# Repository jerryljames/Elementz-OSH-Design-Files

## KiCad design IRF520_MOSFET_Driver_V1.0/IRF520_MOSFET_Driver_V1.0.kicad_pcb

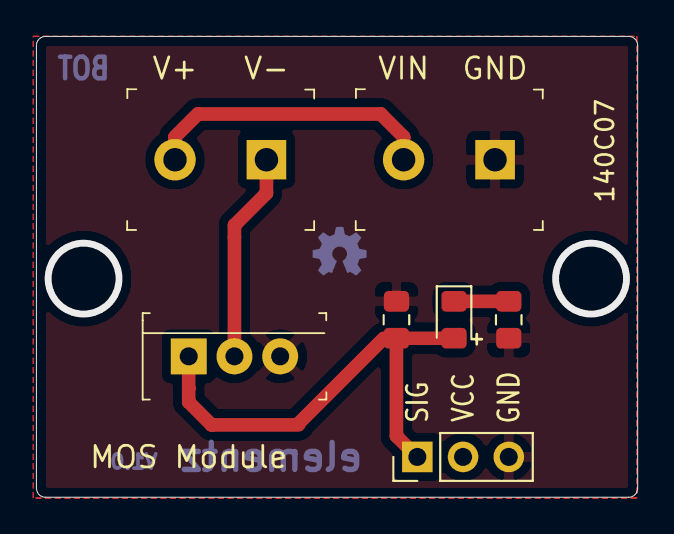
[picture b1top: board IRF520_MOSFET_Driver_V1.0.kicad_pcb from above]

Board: 2 copper layers, 33.4 x 25.6 mm, 7 parts (0 on the bottom side), 5 nets.

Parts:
D1: RED; LED_0805_2012Metric_Pad1.15x1.40mm_HandSolder
J1: Conn_01x03_Male; PinHeader_1x03_P2.54mm_Vertical
J2, J3: 1935161; Term_Block_1x2_P5.08MM
Q1: IRF520PBF; TO-220-3
R1, R2: 1K; R_0805_2012Metric_Pad1.15x1.40mm_HandSolder

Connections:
/SIG: D1.2, J1.1, Q1.1, R1.1
/V+: J2.2, J3.2
/V-: J2.1, Q1.2
GND: J1.3, J3.1, Q1.3, R1.2, R2.2
unnamed: D1.1, R2.1

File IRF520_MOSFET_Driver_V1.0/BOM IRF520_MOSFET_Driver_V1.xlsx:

Reference | Quantity | Value | Footprint | Category | Description | Digi-Key_PN | Family | MPN | Manufacturer | Status | DK_Datasheet_Link | DK_Detail_Page
D1 | 1 | RED | LED_SMD:LED_0805_2012Metric_Pad1.15x1.40mm_HandSolder
J1 | 1 | Conn_01x03_Male | Connector_PinHeader_2.54mm:PinHeader_1x03_P2.54mm_Horizontal
J2 J3 | 2 | 1935161 | TerminalBlock:TerminalBlock_Altech_AK300-2_P5.00mm | Connectors, Interconnects | TERM BLK 2POS SIDE ENTRY 5MM PCB | 277-1667-ND | Terminal Blocks - Wire to Board | 1935161 | Phoenix Contact | Active | https://media.digikey.com/pdf/Data%20Sheets/Phoenix%20Contac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 | /product-detail/en/phoenix-contact/1935161/277-1667-ND/568614
Q1 | 1 | IRF520PBF | digikey-footprints:TO-220-3 | Discrete Semiconductor Products | MOSFET N-CH 100V 9.2A TO-220-3 | IRF520PBF-ND | Transistors - FETs, MOSFETs - Single | IRF520PBF | Vishay Siliconix | Active
R1 R2 | 2 | 1K | Resistor_SMD:R_0805_2012Metric_Pad1.15x1.40mm_HandSolder

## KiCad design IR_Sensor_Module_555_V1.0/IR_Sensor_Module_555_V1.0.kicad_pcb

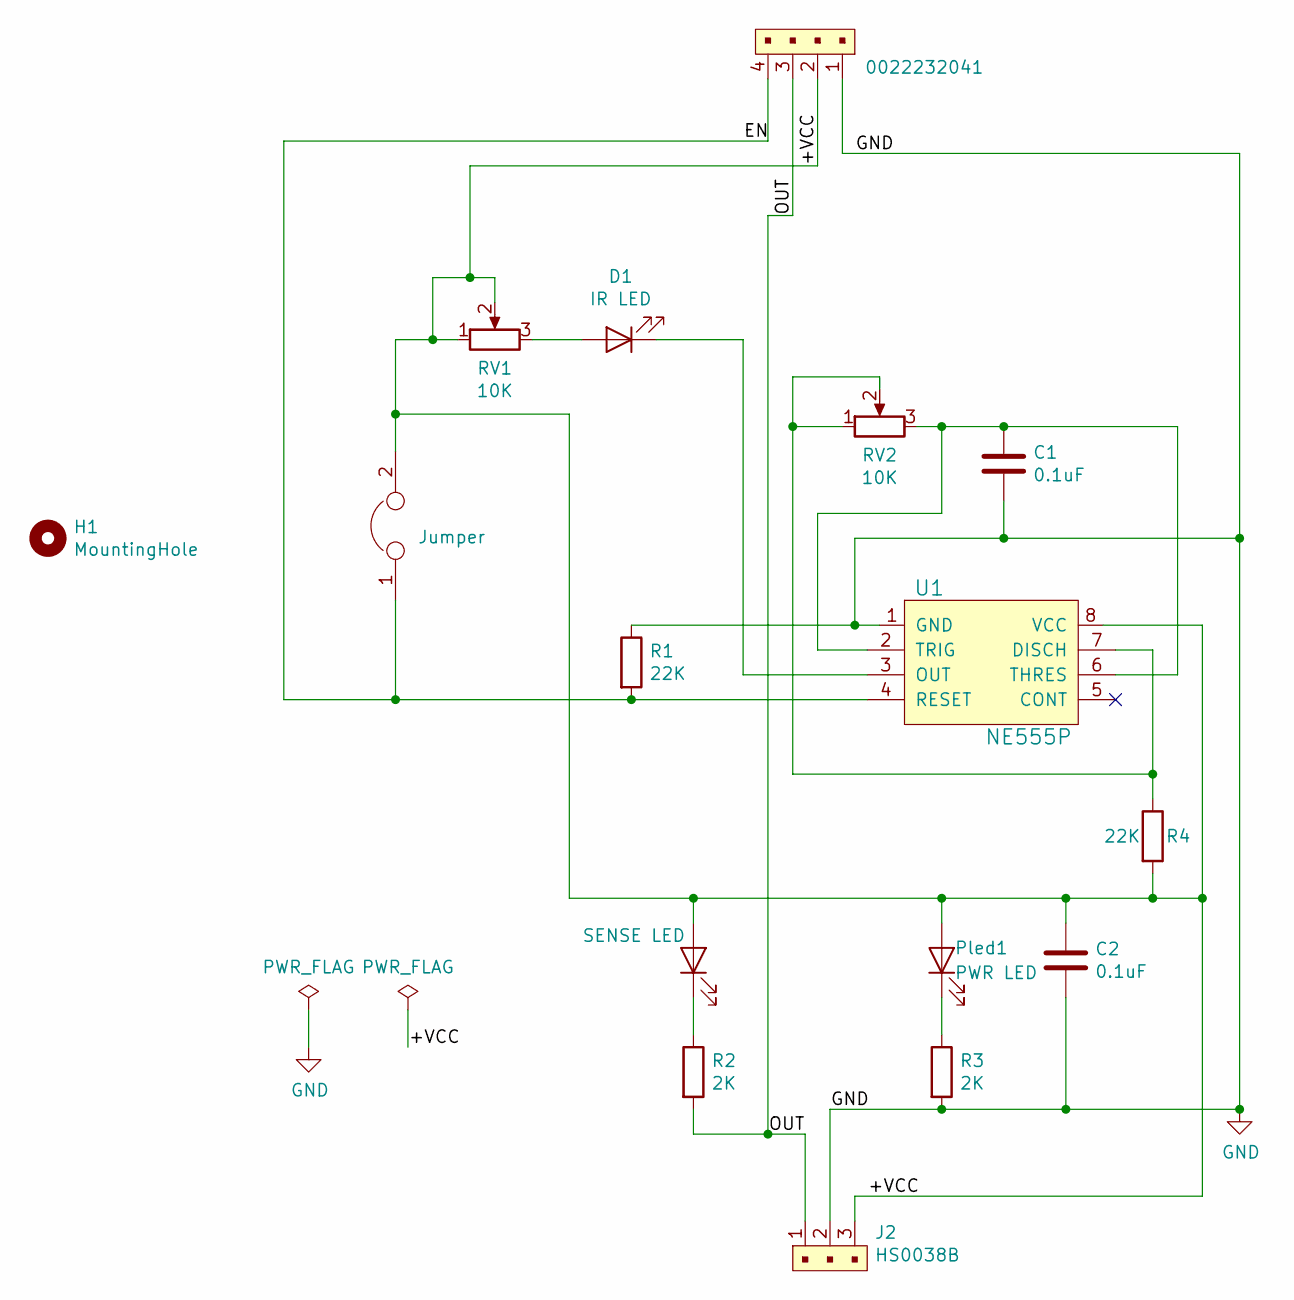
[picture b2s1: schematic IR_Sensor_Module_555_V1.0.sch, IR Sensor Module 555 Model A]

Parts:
C1, C2: 0.1uF; C_0805_2012Metric
D1: IR LED; LED_D5.0mm
H1: MountingHole; MountingHole_3.2mm_M3
J1: 0022232041; PinHeader_1x04_P2.54mm_Vertical; MPN 0022232041; Digi-Key_PN WM4202-ND
J2: HS0038B; PinHeader_1x3_P2.54_Drill1.1mm; MPN 640456-3; Digi-Key_PN A19470-ND
JP1: Jumper; PinHeader_1x02_P2.54mm_Vertical
Pled1: PWR LED; LED_0805_2012Metric
R1, R4: 22K; R_0805_2012Metric
R2, R3: 2K; R_0805_2012Metric
RV1, RV2: 10K; Potentiometer_Bourns_3339P_Vertical_HandSoldering
Sled1: SENSE LED; LED_0805_2012Metric
U1: NE555P; SOIC-8_W5.3mm; MPN NE555P; Digi-Key_PN 296-1411-5-ND

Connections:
/+VCC: C2.1, J1.2, J2.3, JP1.2, Pled1.2 (A), R4.2, RV1.1, RV1.2, Sled1.2 (A), U1.8 (VCC)
/EN: J1.4, JP1.1, R1.2, U1.4 (RESET)
/OUT: J1.3, J2.1, R2.2
GND: C1.2, C2.2, J1.1, J2.2, R1.1, R3.2, U1.1 (GND)
unnamed: C1.1, RV2.3, U1.2 (TRIG), U1.6 (THRES)
unnamed: D1.1 (K), U1.3 (OUT)
unnamed: D1.2 (A), RV1.3
unnamed: Pled1.1 (K), R3.1
unnamed: R2.1, Sled1.1 (K)
unnamed: R4.1, RV2.1, RV2.2, U1.7 (DISCH)

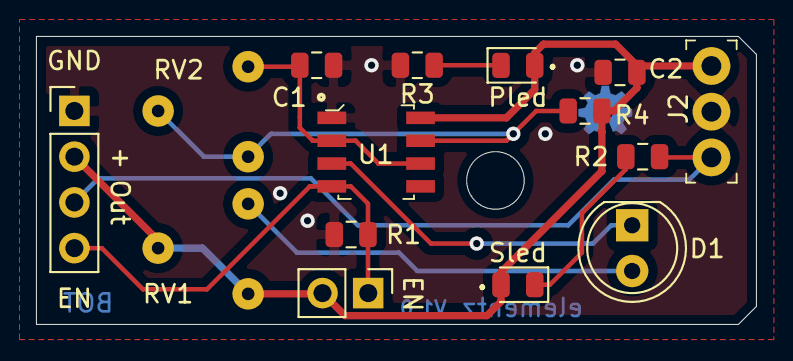
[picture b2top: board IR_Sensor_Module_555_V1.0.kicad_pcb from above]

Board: 2 copper layers, 40.0 x 16.0 mm, 16 parts (0 on the bottom side), 10 nets.

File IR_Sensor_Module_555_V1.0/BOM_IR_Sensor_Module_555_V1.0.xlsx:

Comment | Designator | Footprint
1nF Unpolarized capacitor | C1 | C_0805_2012Metric
0.1uF Unpolarized capacitor | C2 | C_0805_2012Metric
IR LED Light emitting diode | D1 | LED_D5.0mm
Pin Header | J1 | PinHeader_1x04_P2.54mm_Horizontal(90 degree)
HS0038B | J2 | HS0038B 3 Pin
Jumper Jumper, normally closed | JP1 | PinHeader_1x02_P2.54mm_Vertical
Red LED | Pled1 | LED_0805_2012Metric
22K Resistor | R1,R4 | R_0805_2012Metric
2K Resistor | R2,R3 | R_0805_2012Metric
10K Potentiometer | RV1,RV2 | Potentiometer_Bourns_3339P_Vertical_HandSoldering
Green LED | Sled1 | LED_0805_2012Metric
NE555P | U1 | SOIC-8_W5.3mm

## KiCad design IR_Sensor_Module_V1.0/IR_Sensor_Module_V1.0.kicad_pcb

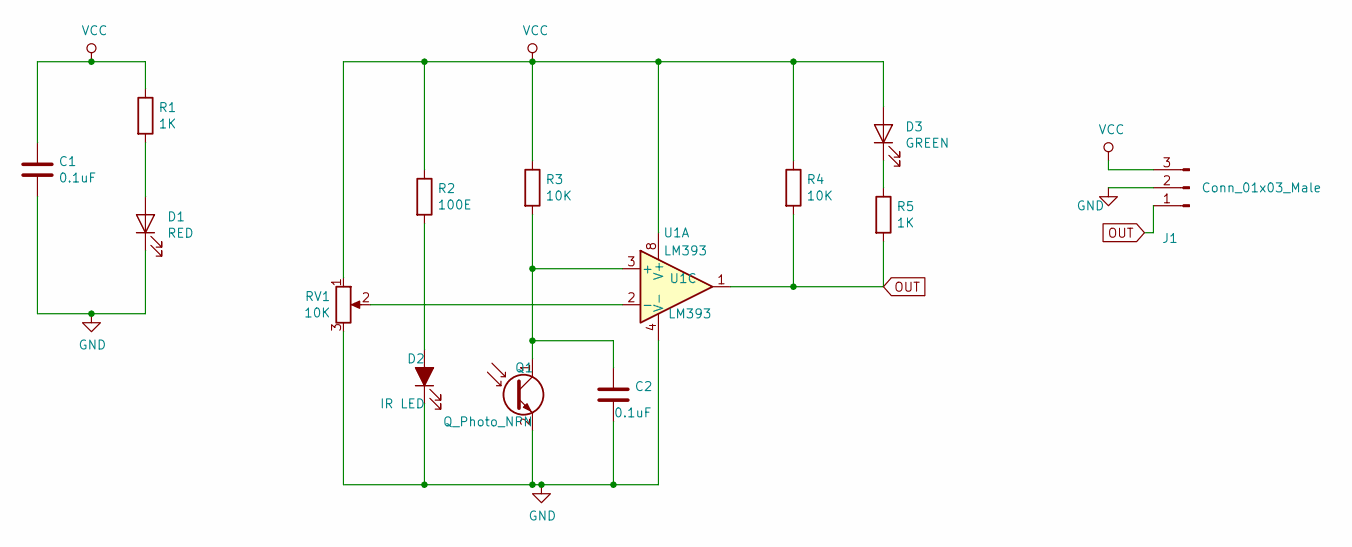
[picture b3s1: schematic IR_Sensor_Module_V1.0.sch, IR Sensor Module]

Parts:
C1, C2: 0.1uF; C_0805_2012Metric_Pad1.15x1.40mm_HandSolder
D1: RED; LED_0805_2012Metric_Pad1.15x1.40mm_HandSolder
D2: IR LED; LED_D5.0mm_Horizontal_O1.27mm_Z3.0mm
D3: GREEN; LED_0805_2012Metric_Pad1.15x1.40mm_HandSolder
J1: Conn_01x03_Male; PinHeader_1x03_P2.54mm_Vertical
Q1: Q_Photo_NPN; LED_D5.0mm_Horizontal_O1.27mm_Z3.0mm
R1, R5: 1K; R_0805_2012Metric_Pad1.15x1.40mm_HandSolder
R2: 100E; R_0805_2012Metric_Pad1.15x1.40mm_HandSolder
R3, R4: 10K; R_0805_2012Metric_Pad1.15x1.40mm_HandSolder
RV1: 10K; Potentiometer_Vishay_T73YP_Vertical
U1: LM393; SOIC-8-1EP_3.9x4.9mm_P1.27mm_EP2.29x3mm

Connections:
GND: C1.2, C2.2, D1.1 (K), D2.1 (K), J1.2, Q1.2 (E), RV1.3, U1.4 (V-)
unnamed: C2.1, Q1.1 (C), R3.2, U1.3 (+)
unnamed: D1.2 (A), R1.2
unnamed: D2.2 (A), R2.2
unnamed: D3.1 (K), R5.1
unnamed: RV1.2, U1.2 (-)
OUT: J1.1, R4.2, R5.2, U1.1
VCC: C1.1, D3.2 (A), J1.3, R1.1, R2.1, R3.1, R4.1, RV1.1, U1.8 (V+)

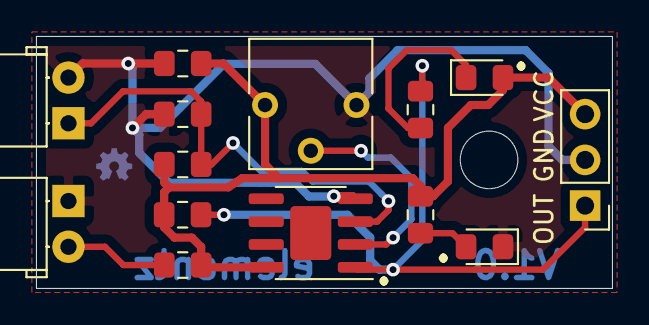
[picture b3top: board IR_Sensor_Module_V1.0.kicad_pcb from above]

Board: 2 copper layers, 32.0 x 14.0 mm, 14 parts (0 on the bottom side), 8 nets.

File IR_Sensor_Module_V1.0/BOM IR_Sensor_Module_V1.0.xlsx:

Comment | Designator | Footprint | LCSC_PART
0.1uF Unpolarized capacitor | C1,C2 | C_0805_2012Metric_Pad1.15x1.40mm_HandSolder
RED Light emitting diode | D1 | LED_0805_2012Metric_Pad1.15x1.40mm_HandSolder
IR LED Light emitting diode, filled shape | D2 | LED_D5.0mm_Horizontal_O1.27mm_Z3.0mm
GREEN Light emitting diode | D3 | LED_0805_2012Metric_Pad1.15x1.40mm_HandSolder
Conn_01x03_Male Generic connector, single row, 01x03, Horizontal | J1 | PinHeader_1x03_P2.54mm_Horizontal(90 degree)
Q_Photo_NPN NPN phototransistor, collector/emitter | Q1 | LED_D5.0mm_Horizontal_O1.27mm_Z3.0mm
1K Resistor | R1,R5 | R_0805_2012Metric_Pad1.15x1.40mm_HandSolder
100E Resistor | R2 | R_0805_2012Metric_Pad1.15x1.40mm_HandSolder
10K Resistor | R3,R4 | R_0805_2012Metric_Pad1.15x1.40mm_HandSolder
10K Potentiometer | RV1 | Potentiometer_Vishay_T73YP_Vertical
LM393 Low-Power, Low-Offset Voltage, Dual Comparators | U1 | SOIC-8-1EP_3.9x4.9mm_P1.27mm_EP2.29x3mm

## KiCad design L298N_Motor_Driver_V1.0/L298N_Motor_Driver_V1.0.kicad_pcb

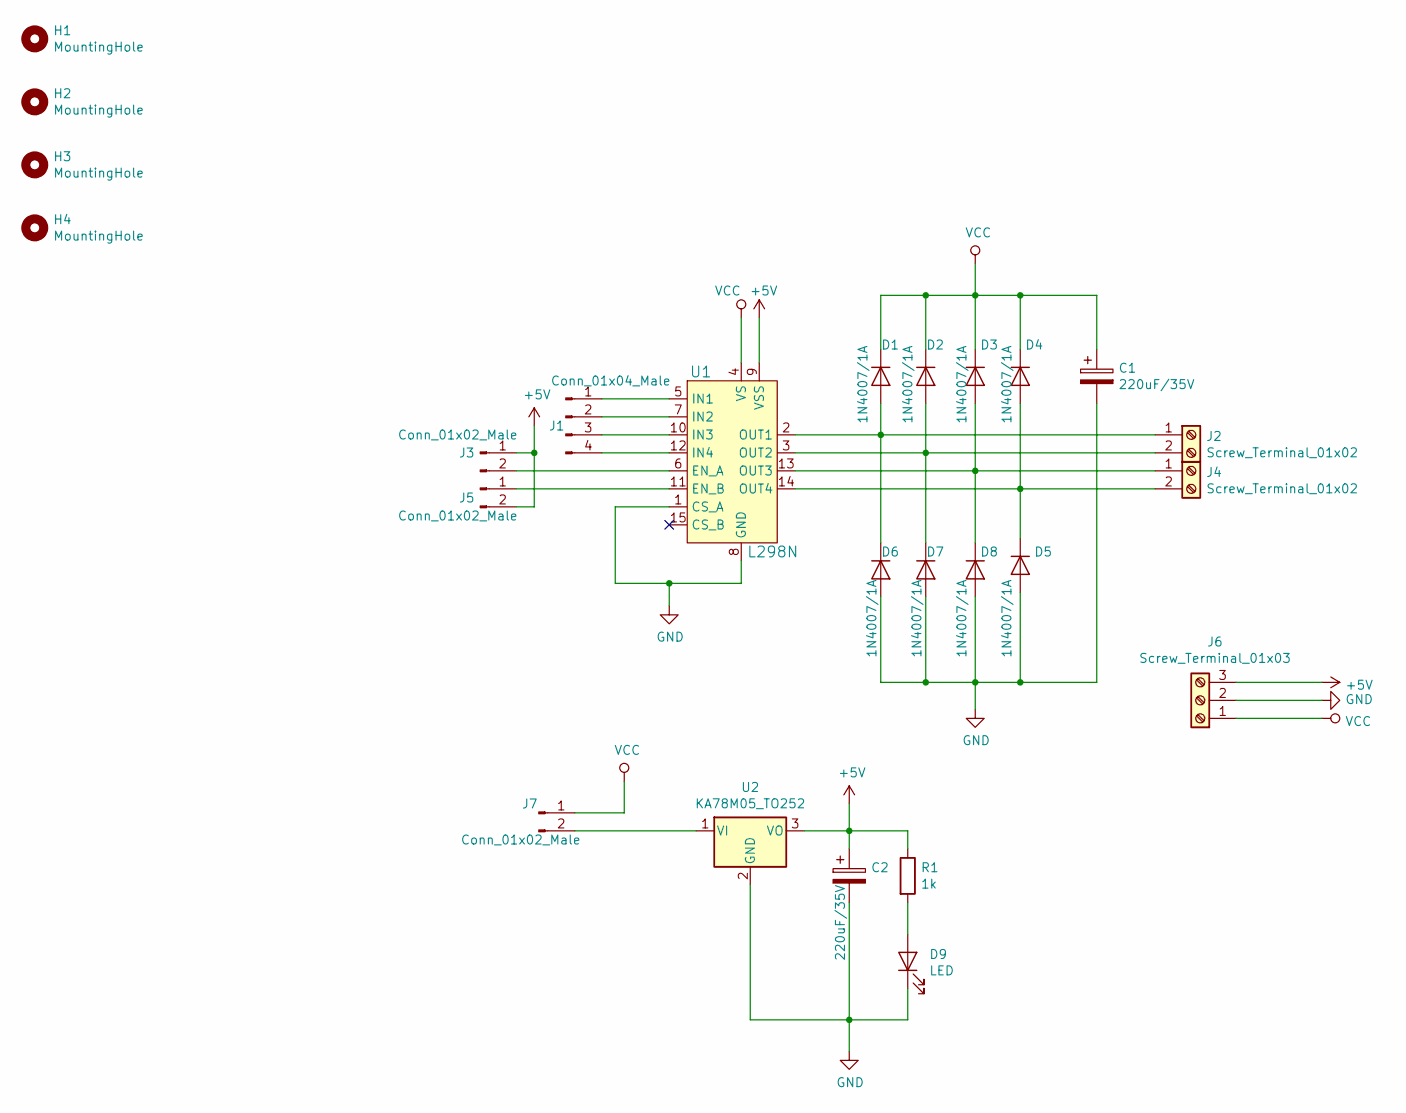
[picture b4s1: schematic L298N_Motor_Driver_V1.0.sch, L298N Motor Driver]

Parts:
C1, C2: 220uF/35V; CP_Elec_6.3x7.7; LCSC_PART C401734
D1, D2, D3, D4, D5, D6, D7, D8: 1N4007/1A; DO-214AC
D9: LED; LED_0805_2012Metric
H1, H2, H3, H4: MountingHole; MountingHole_2.5mm
J1: Conn_01x04_Male; PinHeader_1x04_P2.54mm_Vertical
J2, J4: Screw_Terminal_01x02; TerminalBlock_bornier-2_P5.08mm
J3, J5, J7: Conn_01x02_Male; PinHeader_1x02_P2.54mm_Vertical
J6: Screw_Terminal_01x03; TerminalBlock_bornier-3_P5.08mm
R1: 1k; R_0805_2012Metric
U1: L298N; Multiwatt-15; MPN L298N; Digi-Key_PN 497-1395-5-ND
U2: KA78M05_TO252; TO-252-2

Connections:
+5V: C2.1, J3.1, J5.2, J6.3, R1.1, U1.9 (VSS), U2.3 (VO)
GND: C1.2, C2.2, D5.2 (A), D6.2 (A), D7.2 (A), D8.2 (A), D9.1 (K), J6.2, U1.1 (CS_A), U1.8 (GND), U1.16, U2.2 (GND)
unnamed: D1.2 (A), D6.1 (K), J2.1, U1.2 (OUT1)
unnamed: D2.2 (A), D7.1 (K), J2.2, U1.3 (OUT2)
unnamed: D3.2 (A), D8.1 (K), J4.1, U1.13 (OUT3)
unnamed: D4.2 (A), D5.1 (K), J4.2, U1.14 (OUT4)
unnamed: D9.2 (A), R1.2
unnamed: J1.1, U1.5 (IN1)
unnamed: J1.2, U1.7 (IN2)
unnamed: J1.3, U1.10 (IN3)
unnamed: J1.4, U1.12 (IN4)
unnamed: J3.2, U1.6 (EN_A)
unnamed: J5.1, U1.11 (EN_B)
unnamed: J7.2, U2.1 (VI)
VCC: C1.1, D1.1 (K), D2.1 (K), D3.1 (K), D4.1 (K), J6.1, J7.1, U1.4 (VS)

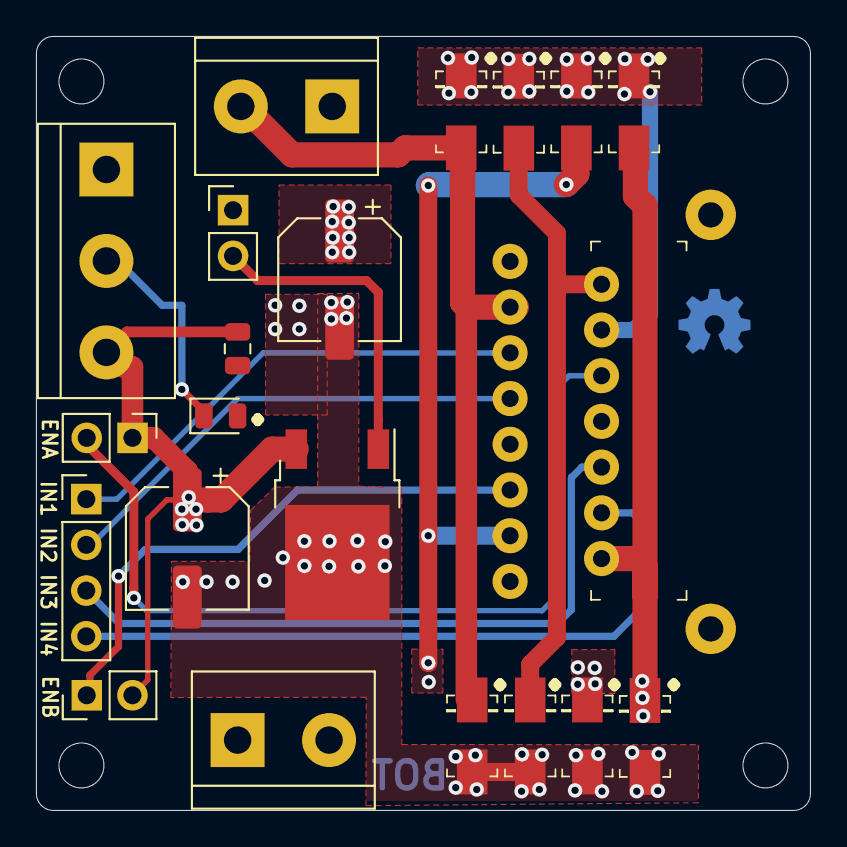
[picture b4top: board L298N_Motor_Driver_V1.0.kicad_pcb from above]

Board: 2 copper layers, 43.0 x 43.0 mm, 25 parts (0 on the bottom side), 15 nets.

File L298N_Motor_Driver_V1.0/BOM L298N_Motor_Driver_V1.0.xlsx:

Comment | Designator | Footprint
220uF/35V Polarized capacitor | C1,C2 | CP_Elec_6.3x7.7
1N4007/1A Diode | D1,D2,D3,D4,D5,D6,D7,D8 | DO-214AC
Red LED | D9 | LED_0805_2012Metric
Conn_01x04_Male Generic connector, single row, 01x04 | J1 | PinHeader_1x04_P2.54mm_Vertical
Screw_Terminal_01x02 Generic screw terminal, single row, 01x02 | J2,J4 | TerminalBlock_bornier-2_P5.08mm
Conn_01x02_Male Generic connector, single row, 01x02 | J3,J5,J7 | PinHeader_1x02_P2.54mm_Vertical
Screw_Terminal_01x03 Generic screw terminal, single row | J6 | TerminalBlock_bornier-3_P5.08mm
1K Resistor | R1 | R_0805_2012Metric
L298N Motordriver | U1 | Multiwatt-15
7805_TO252 | U2 | TO-252-2

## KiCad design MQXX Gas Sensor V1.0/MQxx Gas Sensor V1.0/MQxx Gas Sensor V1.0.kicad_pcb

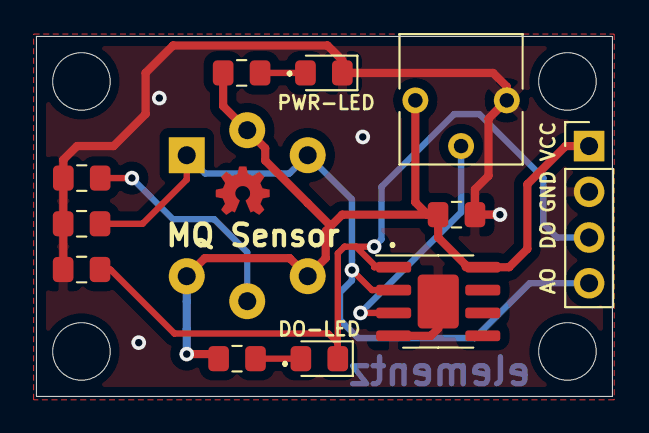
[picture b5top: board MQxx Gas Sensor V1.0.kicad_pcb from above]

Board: 2 copper layers, 32.0 x 20.0 mm, 12 parts (1 on the bottom side), 8 nets.

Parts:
C1, C2: 0.1uF; C_0805_2012Metric_Pad1.15x1.40mm_HandSolder
D1: PWR_LED; LED_0805_2012Metric_Pad1.15x1.40mm_HandSolder
D2: DO_LED; LED_0805_2012Metric_Pad1.15x1.40mm_HandSolder
J1: Conn_01x04_Male; PinHeader_1x04_P2.54mm_Vertical
R1, R2: 1K; R_0805_2012Metric_Pad1.15x1.40mm_HandSolder
R3: 5.1E; R_0805_2012Metric_Pad1.15x1.40mm_HandSolder
R4: 4.7K; R_0805_2012Metric_Pad1.15x1.40mm_HandSolder
RV1: 10K; Potentiometer_Vishay_T73YP_Vertical
U1: LM393; SOIC-8-1EP_3.9x4.9mm_P1.27mm_EP2.29x3mm
U?1: MQ-X; MQ-6

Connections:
+5V: C2.1, J1.1, R1.1, R2.1, RV1.1, U1.8, U?1.2, U?1.4, U?1.6
AOUT: J1.4, R4.1, U1.2, U?1.1, U?1.3
DOUT: C1.1, D2.1, J1.3, U1.1
GND: C1.2, C2.2, D1.1, J1.2, R3.2, R4.2, RV1.3, U1.4, U1.9
unnamed: D1.2, R1.2
unnamed: D2.2, R2.2
unnamed: R3.1, U?1.5
unnamed: RV1.2, U1.3

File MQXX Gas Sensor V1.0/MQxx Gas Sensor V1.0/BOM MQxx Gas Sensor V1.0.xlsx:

Comment | Designator | Footprint
0.1uF Unpolarized capacitor | C1,C2 | C_0805_2012Metric_Pad1.15x1.40mm_HandSolder
PWR_LED RED | D1 | LED_0805_2012Metric_Pad1.15x1.40mm_HandSolder
DO_LED GREEN | D2 | LED_0805_2012Metric_Pad1.15x1.40mm_HandSolder
Conn_01x04_Male Generic connector, single row, 01x04 | J1 | PinHeader_1x04_P2.54mm_Horizontal(90 degree)
1K Resistor | R1,R2 | R_0805_2012Metric_Pad1.15x1.40mm_HandSolder
5.1E Resistor | R3 | R_0805_2012Metric_Pad1.15x1.40mm_HandSolder
4.7K Resistor | R4 | R_0805_2012Metric_Pad1.15x1.40mm_HandSolder
10K Potentiometer | RV1 | Potentiometer_Vishay_T73YP_Vertical
LM393 Dual operational amplifier | U1 | SOIC-8-1EP_3.9x4.9mm_P1.27mm_EP2.29x3mm
MQ-X Semiconductor Sensor for Flammable Gas | U?1 | MQ-X
